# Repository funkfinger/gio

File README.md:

# gio

A 2 HP Eurorack generative arpeggiator module built around the Seeed XIAO RP2350. Produces scale-quantised V/Oct pitch CV and gate outputs driven by a probability-layered generative engine. Open-source hardware and firmware.

Spiritual successor to [funkfinger/xiao-ra4m1-arp](https://github.com/funkfinger/xiao-ra4m1-arp), ported to the RP2350 with an encoder + OLED UI and an external I2C DAC (MCP4725) in place of the RA4M1's onboard DAC.

## Status

**Planning / pre-prototype.** No hardware fabricated yet; no firmware released. See [`docs/decisions.md`](docs/decisions.md) for the bring-up plan and [`docs/stories/`](docs/stories/) for the story-driven development backlog.

## Repo layout

```
gio/
├── firmware/arp/     PlatformIO project for the arpeggiator firmware
├── hardware/         KiCad project — populated post-breadboard validation
├── docs/             Specification, decisions, user stories
└── CHANGELOG.md      Keep a Changelog format; updated on every commit
```

## Documentation

- **[Specification](docs/generative-arp-module.md)** — hardware spec, firmware architecture, BOM, calibration
- **[Decisions](docs/decisions.md)** — tooling, scope, workflow, licensing, versioning
- **[Stories](docs/stories/)** — user-story-driven development backlog

## Toolchain

- **Firmware:** [PlatformIO](https://platformio.org/) with the earlephilhower Arduino-Pico platform (`board = seeed_xiao_rp2350`)
- **Tests:** host-side unit tests via `pio test -e native` for pure-logic modules (scales, arp, tempo). HAL is bench-verified.
- **Hardware:** KiCad (project deferred — see decisions)
- **CI:** GitHub Actions runs host tests on push and PR

## Versioning

- **Firmware:** [Semantic Versioning](https://semver.org/), scoped tags per firmware: `arp/v0.1.0`
- **Hardware:** `Rev N.M` notation, silkscreened on the PCB
- **Docs:** unversioned; history lives in `git log`

See [decisions §12](docs/decisions.md) for full rules.

## Licensing

| Area | License | File |
|---|---|---|
| Firmware | MIT | [`LICENSE-firmware`](LICENSE-firmware) |
| Hardware (KiCad, panel artwork) | Apache 2.0 | [`LICENSE-hardware`](LICENSE-hardware) |
| Documentation | CC-BY 4.0 | [`LICENSE-docs`](LICENSE-docs) |

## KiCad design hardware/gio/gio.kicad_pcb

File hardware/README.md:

# hardware/

KiCad schematic and PCB for the gio module.

**This directory is intentionally empty until breadboard validation is complete.**

Per `docs/decisions.md` §7: the KiCad project is deferred until the breadboard signal chain (MCP4725 → MCP6002 → V/Oct output) is validated within ±2 mV of target voltages and the I2C bus sharing between DAC and OLED is confirmed clean.

The gate resistor value (R4) was a known source of V/Oct loading error in the predecessor project — confirmed to 100 Ω before PCB layout begins.

When ready, this directory will contain:

```
hardware/
├── gio.kicad_pro
├── gio.kicad_sch
├── gio.kicad_pcb
├── panel/
│   └── gio-panel.kicad_pcb
├── gerbers/
│   └── (generated outputs for JLCPCB)
└── bom/
    └── gio-bom.csv
```

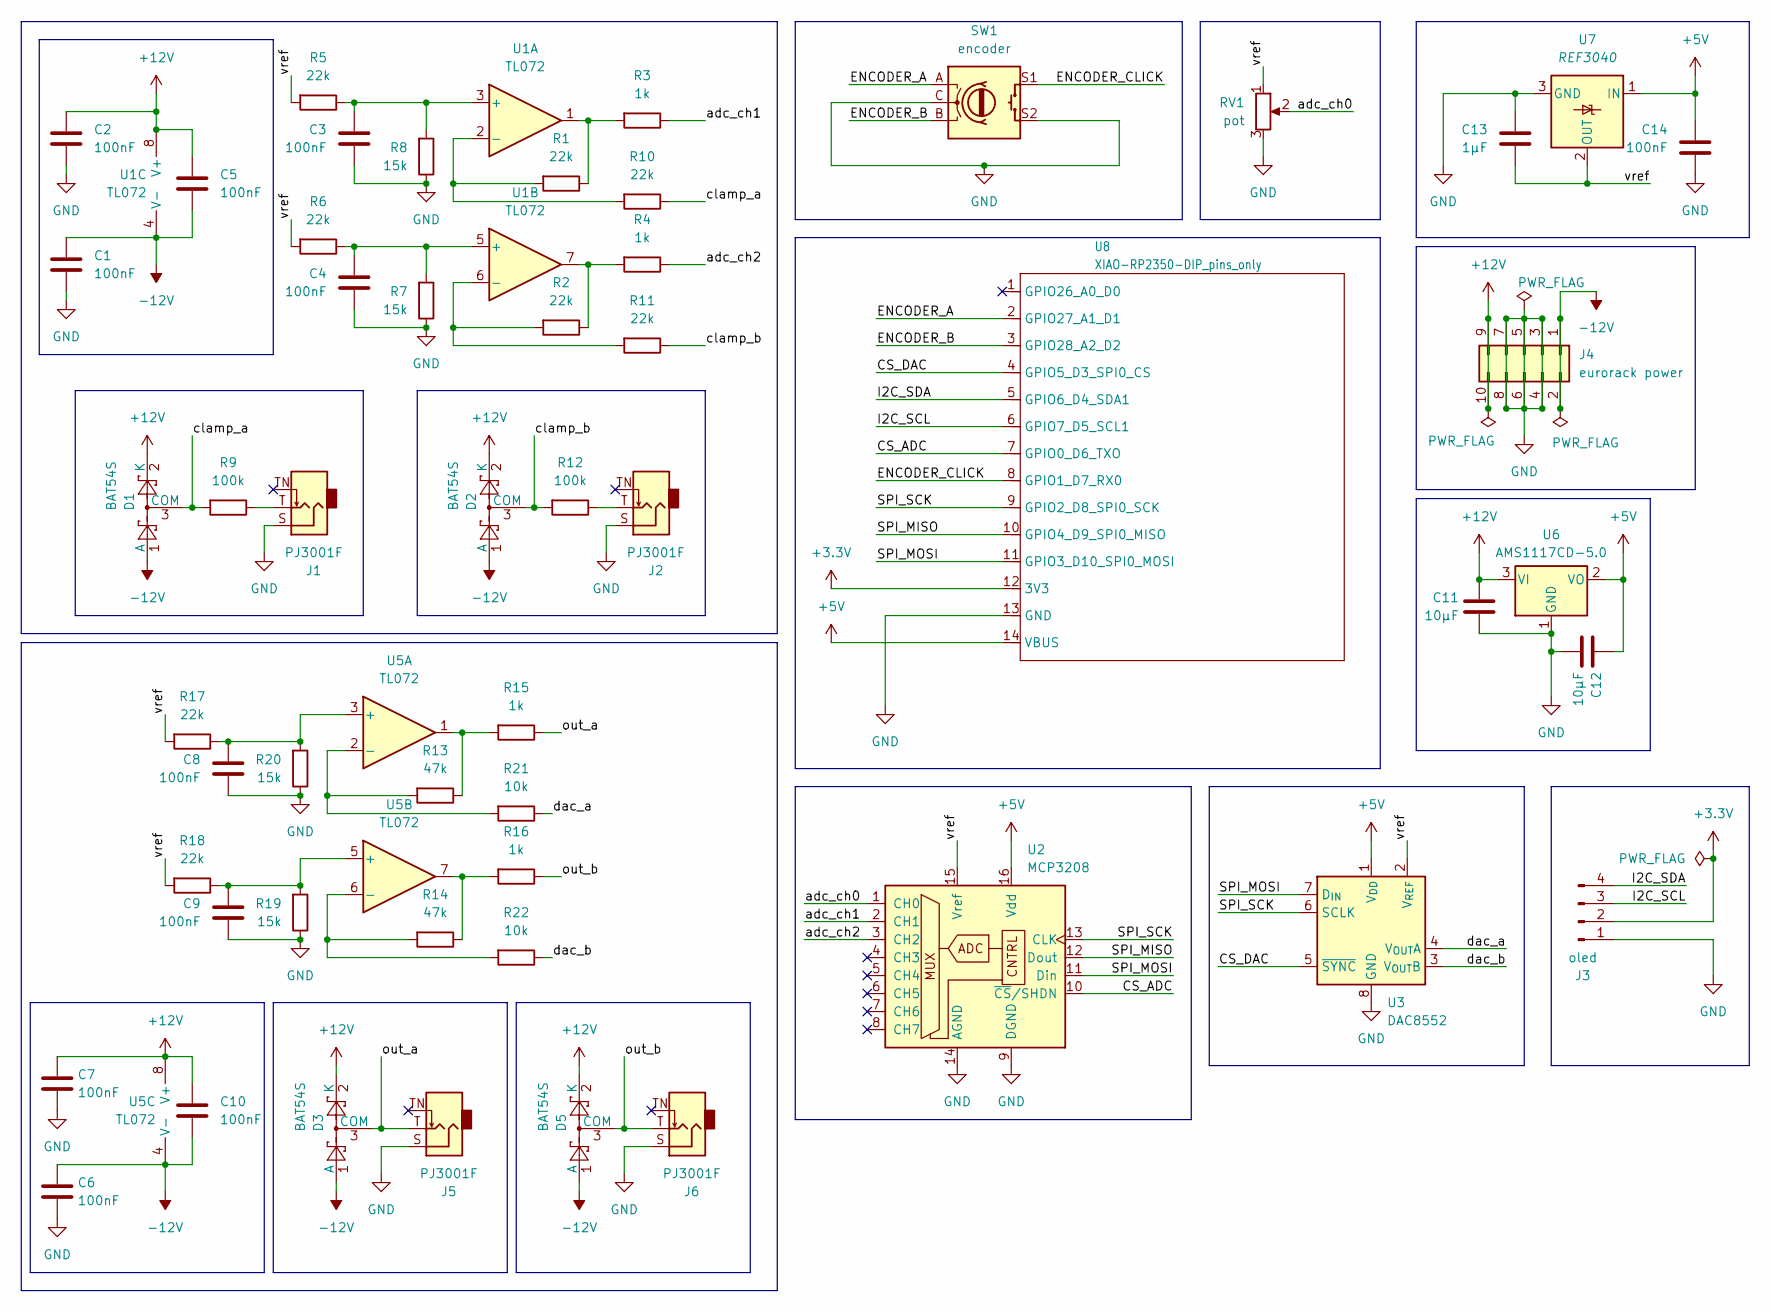
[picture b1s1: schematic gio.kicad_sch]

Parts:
C1, C2, C3, C4, C5, C6, C7, C8, C9, C10, C14: 100nF; C_0603_1608Metric
C11, C12: 10µF; C_0603_1608Metric
C13: 1µF; C_0603_1608Metric
D1, D2, D3, D5: BAT54S; SOT-23
J1, J2, J5, J6: PJ3001F; Jack_3.5mm_QingPu_WQP-PJ398SM_Vertical_CircularHoles
J3: oled; PinSocket_1x04_P2.54mm_Vertical
J4: eurorack power; IDC-Header_2x05_P2.54mm_Vertical
R1, R2, R5, R6, R10, R11, R17, R18: 22k; R_0603_1608Metric
R3, R4, R15, R16: 1k; R_0603_1608Metric
R7, R8, R19, R20: 15k; R_0603_1608Metric
R9, R12: 100k; R_0603_1608Metric
R13, R14: 47k; R_0603_1608Metric
R21, R22: 10k; R_0603_1608Metric
RV1: pot; Potentiometer_RV09
SW1: encoder; RotaryEncoder_Bourns_Vertical_PEC12R-3x17F-Sxxxx
U1, U5: TL072; SO-8_3.9x4.9mm_P1.27mm
U2: MCP3208; SOIC-16_3.9x9.9mm_P1.27mm
U3: DAC8552; Texas_S-PDSO-G8_3x3mm_P0.65mm
U6: AMS1117CD-5.0; SOT-223
U7: REF3040; SOT-23
U8: XIAO-RP2350-DIP_pins_only

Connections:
+3.3V: J3.2, U8.12 (3V3)
+5V: C12.1, C14.1, U2.16 (Vdd), U3.1 (V_{DD}), U6.2 (VO), U7.1 (IN), U8.14 (VBUS)
+12V: C2.1, C5.1, C7.1, C10.1, C11.1, D1.2 (K), D2.2 (K), D3.2 (K), D5.2 (K), J4.9, J4.10, U1.8 (V+), U5.8 (V+), U6.3 (VI)
-12V: C1.1, C5.2, C6.1, C10.2, D1.1 (A), D2.1 (A), D3.1 (A), D5.1 (A), J4.1, J4.2, U1.4 (V-), U5.4 (V-)
/CS_ADC: U2.10 (~CS/SHDN), U8.7 (GPIO0_D6_TXO)
/CS_DAC: U3.5 (~SYNC), U8.4 (GPIO5_D3_SPI0_CS)
/ENCODER_A: SW1.A, U8.2 (GPIO27_A1_D1)
/ENCODER_B: SW1.B, U8.3 (GPIO28_A2_D2)
/ENCODER_CLICK: SW1.S1, U8.8 (GPIO1_D7_RX0)
/I2C_SCL: J3.3, U8.6 (GPIO7_D5_SCL1)
/I2C_SDA: J3.4, U8.5 (GPIO6_D4_SDA1)
/SPI_MISO: U2.12 (Dout), U8.10 (GPIO4_D9_SPI0_MISO)
/SPI_MOSI: U2.11 (Din), U3.7 (D_{IN}), U8.11 (GPIO3_D10_SPI0_MOSI)
/SPI_SCK: U2.13 (CLK), U3.6 (SCLK), U8.9 (GPIO2_D8_SPI0_SCK)
/adc_ch0: RV1.2, U2.1 (CH0)
/adc_ch1: R3.1, U2.2 (CH1)
/adc_ch2: R4.1, U2.3 (CH2)
/clamp_a: D1.3 (COM), R9.2, R10.1
/clamp_b: D2.3 (COM), R11.1, R12.2
/dac_a: R21.1, U3.4 (V_{OUT}A)
/dac_b: R22.1, U3.3 (V_{OUT}B)
/out_a: D3.3 (COM), J5.T, R15.1
/out_b: D5.3 (COM), J6.T, R16.1
/vref: C13.2, R5.2, R6.2, R17.2, R18.2, RV1.1, U2.15 (Vref), U3.2 (V_{REF}), U7.2 (OUT)
GND: C1.2, C2.2, C3.2, C4.2, C6.2, C7.2, C8.2, C9.2, C11.2, C12.2, C13.1, C14.2, J1.S, J2.S, J3.1, J4.3, J4.4, J4.5, J4.6, J4.7, J4.8, J5.S, J6.S, R7.1, R8.1, R19.1, R20.1, RV1.3, SW1.C, SW1.S2, U2.9 (DGND), U2.14 (AGND), U3.8 (GND), U6.1 (GND), U7.3 (GND), U8.13 (GND)
unnamed: J1.T, R9.1
unnamed: J2.T, R12.1
unnamed: R1.1, R3.2, U1.1
unnamed: R2.1, R4.2, U1.7
unnamed: R13.1, R15.2, U5.1
unnamed: R14.1, R16.2, U5.7
unnamed: C3.1, R5.1, R8.2, U1.3 (+)
unnamed: R1.2, R10.2, U1.2 (-)
unnamed: C4.1, R6.1, R7.2, U1.5 (+)
unnamed: R2.2, R11.2, U1.6 (-)
unnamed: C8.1, R17.1, R20.2, U5.3 (+)
unnamed: R13.2, R21.2, U5.2 (-)
unnamed: C9.1, R18.1, R19.2, U5.5 (+)
unnamed: R14.2, R22.2, U5.6 (-)

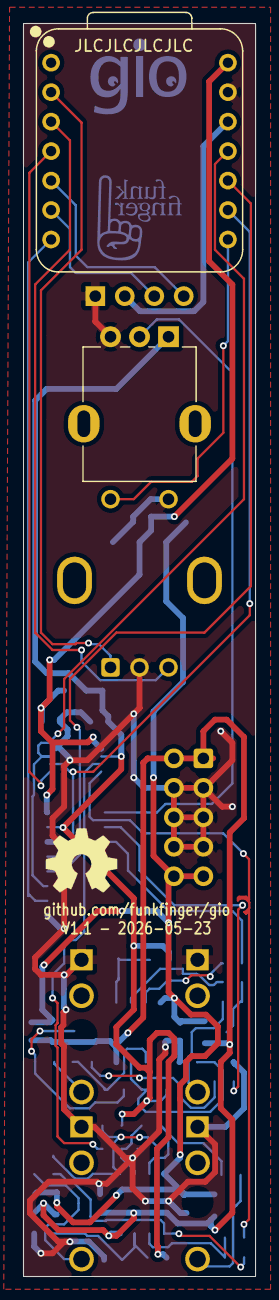
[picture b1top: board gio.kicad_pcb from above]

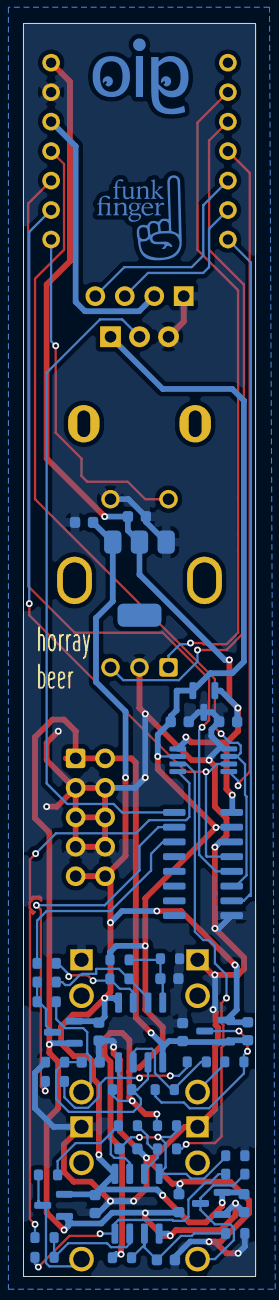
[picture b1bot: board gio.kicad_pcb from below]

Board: 2 copper layers, 20.0 x 108.0 mm, 57 parts (50 on the bottom side), 39 nets.

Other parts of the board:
funkfinger logo 9mm: funkfinger logo 9mm; funkfinger-logo-9mm-copper-mask
gio logo: gio-logo-front-copper-mask

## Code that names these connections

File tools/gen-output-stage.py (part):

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  - R_iso (1k) repurposed as R_jack_series 1k.
  - New output clamps (BAT54S) placed AFTER R_jack_series, BEFORE jack.
  - New output jacks (J3, J4) placed to the right of clamps.
  - DAC output labels (dac_a, dac_b) replace the input clamp_a/clamp_b nets.
"""

import re
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    # topology because the signal flow reverses direction:
    #   - In input: jack -> R_series -> [clamp_a node] -> R_in -> op-amp -> R_iso -> [adc_ch1]
    #   - In output: [dac_a] -> R_in -> op-amp -> R_jack_series -> [out_a] -> jack
    # The label that was at R_in's "outer" pin (clamp_a) is now where DAC enters.
    # The label that was at R_iso's "outer" pin (adc_ch1) is now where signal exits to jack.
    "clamp_a": "dac_a",   # at R21 (R_in ch A) right pin = DAC signal input
    "clamp_b": "dac_b",
    "adc_ch1": "out_a",   # at R15 (R_jack_series ch A) right pin = jack output
    "adc_ch2": "out_b",
}

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            next_pwr += 1
        new_block = remap_reference(new_block, ref, power_renumber[ref])

    # Rename labels (clamp_a → out_a, etc.)
    if kind == "label":
        for old, new in LABEL_RENAMES.items():
            new_block = rename_label(new_block, old, new)
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
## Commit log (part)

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2026-04-21 feat: scaffold gio — XIAO RP2350 generative arpeggiator
    Port of xiao-ra4m1-arp to the XIAO RP2350 with the encoder+OLED UI
    as baseline (not a retrofit). Establishes the full project structure,
    spec, decisions, user story backlog (stories 001–008), firmware
    scaffold, CI, and license files.
    Key differences from the RA4M1 predecessor:
    - MCP4725 I2C DAC replaces the RA4M1's onboard DAC
2026-04-21 docs: replace MCP4725 I2C DAC with RP2350 PWM + 2-pole RC filter
    Decision made during pin-budget grill-me session. RP2350 12-bit hardware
    PWM on D2 at 36.6 kHz through a 2-pole passive RC filter (2× 10kΩ +
    100nF, f_c ≈ 160 Hz) gives < 63 µV ripple and 5 ms settling — better
    than an I2C DAC and with no bus contention with the OLED.
    Changes:
    - Spec: §2.3 MCP4725 replaced with PWM DAC spec and filter topology;
2026-04-21 docs: lock in 2HP / 4-jack constraint; A3 marked spare
    Q2 of pin-budget grill-me resolved: module is firmly 2HP with a 2×2
    jack layout (J1 clock in, J2 CV in, J3 V/Oct out, J4 gate out). A3
    (GP29) is an unpopulated spare internal pad — no panel jack in Rev 0.1.
    Panel layout note updated to make the 4-jack constraint explicit.
    https://claude.ai/code/session_01XVc7vzNY75HY939djUqTbP
2026-04-21 docs: dual-purpose input jacks; J1 moved to A3 for ADC capability
    Pin-budget grill-me Q3 resolved. Requirement: one trigger in, one V/Oct
    in, dual-purpose if the circuit allows it.
    Both J1 and J2 now use identical hardware — 100 kΩ series + 68 kΩ to
    GND + BAT54 dual Schottky — mapping 0–8V V/Oct to 0–3.24V at ADC (42
    counts/semitone, sufficient for scale quantisation) and clamping
    negatives safely. Firmware selects CLOCK or PITCH mode per jack via the
2026-04-21 docs: millis() non-blocking timing architecture (Path A)
    Pin-budget grill-me Q4 resolved. Gate and step timing uses millis()
    timestamp comparisons rather than delay(). Keeps the main loop free
    to service encoder, OLED updates, pot reads, and external clock edges
    every iteration. Worst-case jitter is ~5.8 ms (full OLED I2C refresh
    on parameter change) vs 50 ms/step at 300 BPM — acceptable for a
    generative arp; hardware timer revisit deferred to bench validation.
2026-04-21 build: pin arduino-pico to 4.4.0; require per-pin analogWriteFreq
    Platform version was tracking `main`, which is a silent reproducibility
    hazard and — more concretely — a risk to the PWM DAC. The PWM V/Oct path
    relies on `analogWriteFreq(pin, freq)` being the per-pin overload, not
    the older global form that would retune every PWM slice in the chip.
    - platformio.ini: pin `earlephilhower/arduino-pico#4.4.0`
    - decisions.md: add §11 "Platform version pinned to a tagged release"
2026-05-06 routing pcb
2026-05-06 just ratsnest - fresh to route
